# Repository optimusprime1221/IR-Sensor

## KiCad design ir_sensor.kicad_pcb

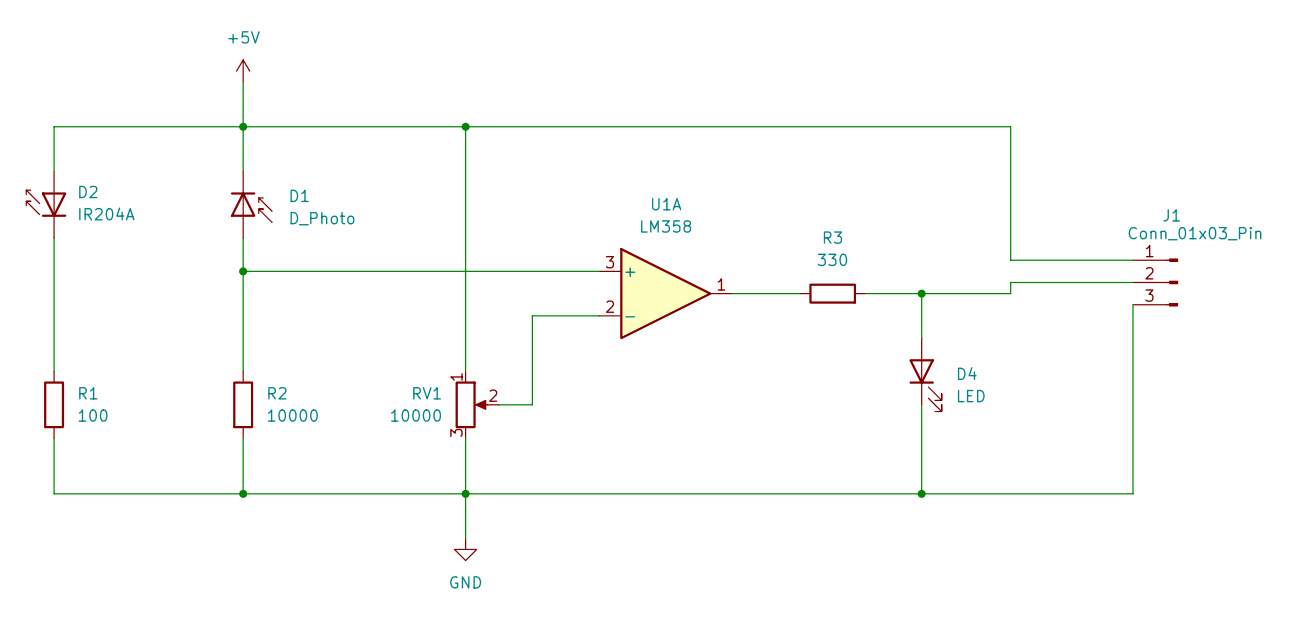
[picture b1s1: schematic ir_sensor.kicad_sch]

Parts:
D1: D_Photo; LED_1W_3W_R8
D2: IR204A; LED_1W_3W_R8
D4: LED; LED_1W_3W_R8
J1: Conn_01x03_Pin; PinHeader_1x03_P2.54mm_Vertical
R1: 100; R_0805_2012Metric
R2: 10000; R_0805_2012Metric
R3: 330; R_0805_2012Metric
RV1: 10000; Potentiometer_ACP_CA9-VSMD_Vertical
U1: LM358; SOIC-8-1EP_3.9x4.9mm_P1.27mm_EP2.514x3.2mm_ThermalVias

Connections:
+5V: D1.1 (K), D2.2 (A), J1.1, RV1.1
GND: D4.1 (K), J1.3, R1.2, R2.2, RV1.3
unnamed: D1.2 (A), R2.1, U1.3 (+)
unnamed: D2.1 (K), R1.1
unnamed: D4.2 (A), J1.2, R3.2
unnamed: R3.1, U1.1
unnamed: RV1.2, U1.2 (-)

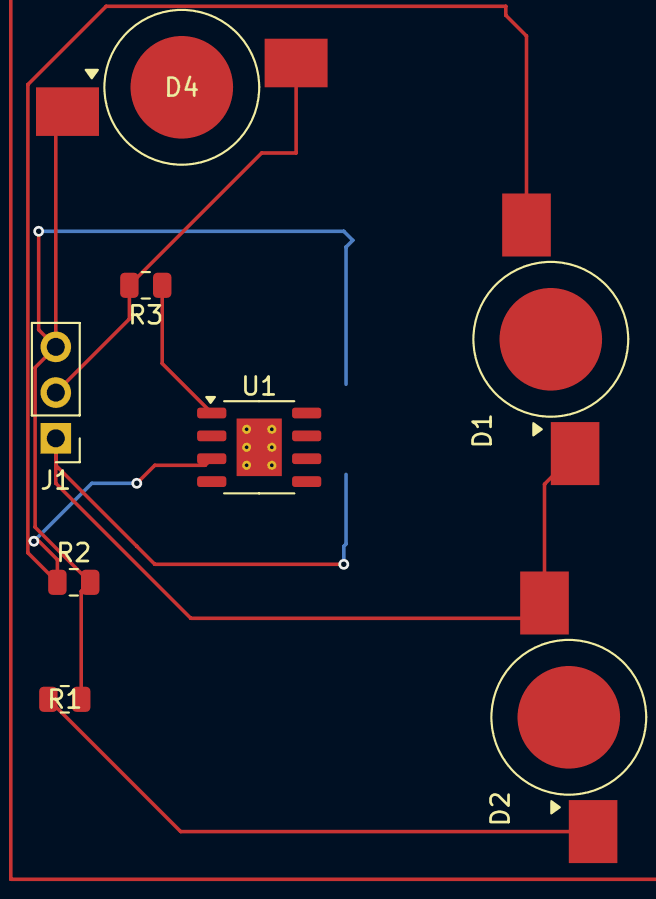
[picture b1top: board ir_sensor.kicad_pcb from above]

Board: 2 copper layers, 9 parts (1 on the bottom side), 7 nets.
